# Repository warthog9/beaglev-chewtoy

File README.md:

This is a fairly simple little board targetted at the BeagleV, but likely usable for anything that uses a 2x20 pin header.

The board takes the existing 2x20 header and either via a through-hole, or smt, header extends it away from the board
(assuming the connetor is on the edge, and rotates it 180deg so if you happen to have a large heat sink, or something
else that's blocking the pins they might still be accessible for hats, etc

# Where to get one built

* OSH Park https://oshpark.com/shared_projects/uNRCdQbW

# License and Copyright
(C) John 'Warthog9' Hawley 2021
CC-BY-SA 4.0

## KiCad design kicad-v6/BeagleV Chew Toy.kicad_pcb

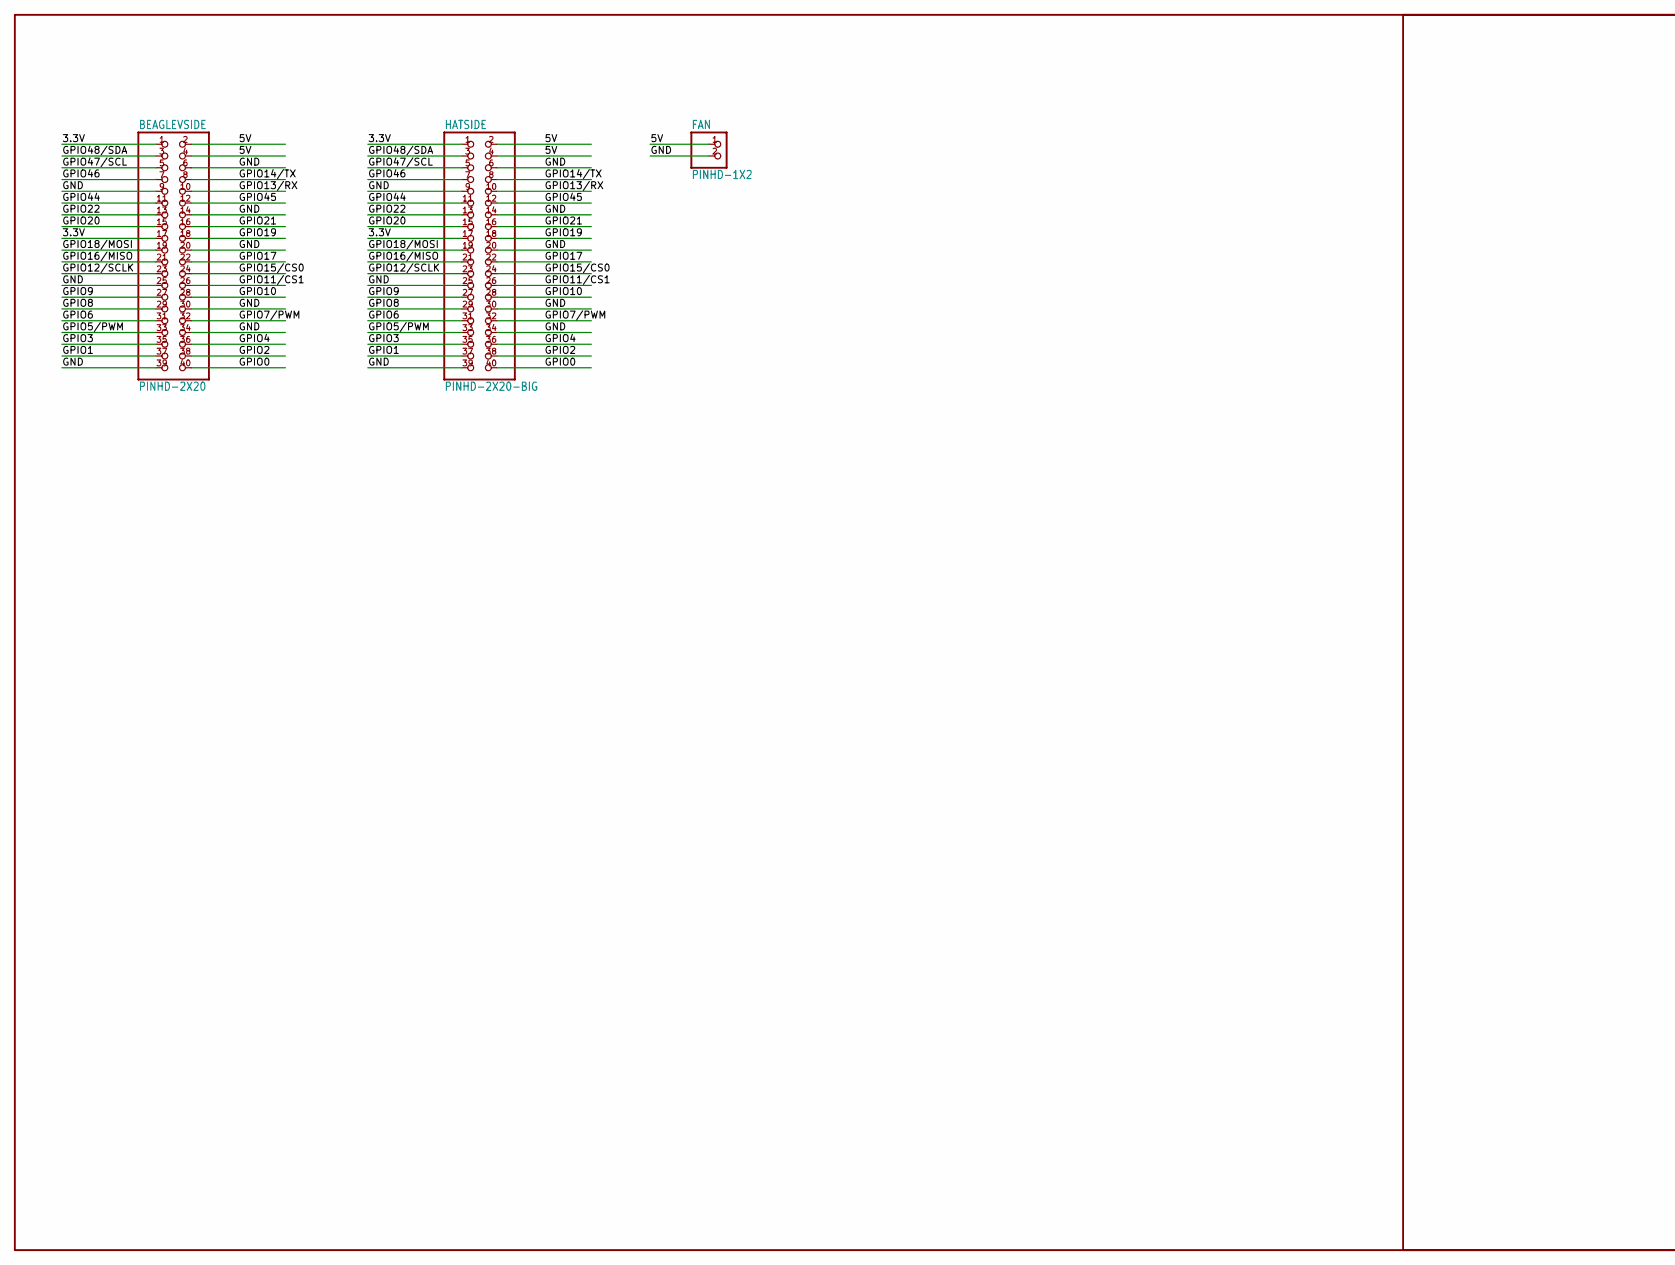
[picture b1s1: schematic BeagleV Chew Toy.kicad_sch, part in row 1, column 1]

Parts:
BEAGLEVSIDE: PINHD-2X20; 2X20
FAN: PINHD-1X2; 1X02
HATSIDE: PINHD-2X20-BIG; 2X20-BIG

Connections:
3.3V: BEAGLEVSIDE.1, BEAGLEVSIDE.17, HATSIDE.1, HATSIDE.17
5V: BEAGLEVSIDE.2, BEAGLEVSIDE.4, FAN.1, HATSIDE.2, HATSIDE.4
GND: BEAGLEVSIDE.6, BEAGLEVSIDE.9, BEAGLEVSIDE.14, BEAGLEVSIDE.20, BEAGLEVSIDE.25, BEAGLEVSIDE.30, BEAGLEVSIDE.34, BEAGLEVSIDE.39, FAN.2, HATSIDE.6, HATSIDE.9, HATSIDE.14, HATSIDE.20, HATSIDE.25, HATSIDE.30, HATSIDE.34, HATSIDE.39
GPIO0: BEAGLEVSIDE.40, HATSIDE.40
GPIO1: BEAGLEVSIDE.37, HATSIDE.37
GPIO2: BEAGLEVSIDE.38, HATSIDE.38
GPIO3: BEAGLEVSIDE.35, HATSIDE.35
GPIO4: BEAGLEVSIDE.36, HATSIDE.36
GPIO5/PWM: BEAGLEVSIDE.33, HATSIDE.33
GPIO6: BEAGLEVSIDE.31, HATSIDE.31
GPIO7/PWM: BEAGLEVSIDE.32, HATSIDE.32
GPIO8: BEAGLEVSIDE.29, HATSIDE.29
GPIO9: BEAGLEVSIDE.27, HATSIDE.27
GPIO10: BEAGLEVSIDE.28, HATSIDE.28
GPIO11/CS1: BEAGLEVSIDE.26, HATSIDE.26
GPIO12/SCLK: BEAGLEVSIDE.23, HATSIDE.23
GPIO13/RX: BEAGLEVSIDE.10, HATSIDE.10
GPIO14/TX: BEAGLEVSIDE.8, HATSIDE.8
GPIO15/CS0: BEAGLEVSIDE.24, HATSIDE.24
GPIO16/MISO: BEAGLEVSIDE.21, HATSIDE.21
GPIO17: BEAGLEVSIDE.22, HATSIDE.22
GPIO18/MOSI: BEAGLEVSIDE.19, HATSIDE.19
GPIO19: BEAGLEVSIDE.18, HATSIDE.18
GPIO20: BEAGLEVSIDE.15, HATSIDE.15
GPIO21: BEAGLEVSIDE.16, HATSIDE.16
GPIO22: BEAGLEVSIDE.13, HATSIDE.13
GPIO44: BEAGLEVSIDE.11, HATSIDE.11
GPIO45: BEAGLEVSIDE.12, HATSIDE.12
GPIO46: BEAGLEVSIDE.7, HATSIDE.7
GPIO47/SCL: BEAGLEVSIDE.5, HATSIDE.5
GPIO48/SDA: BEAGLEVSIDE.3, HATSIDE.3

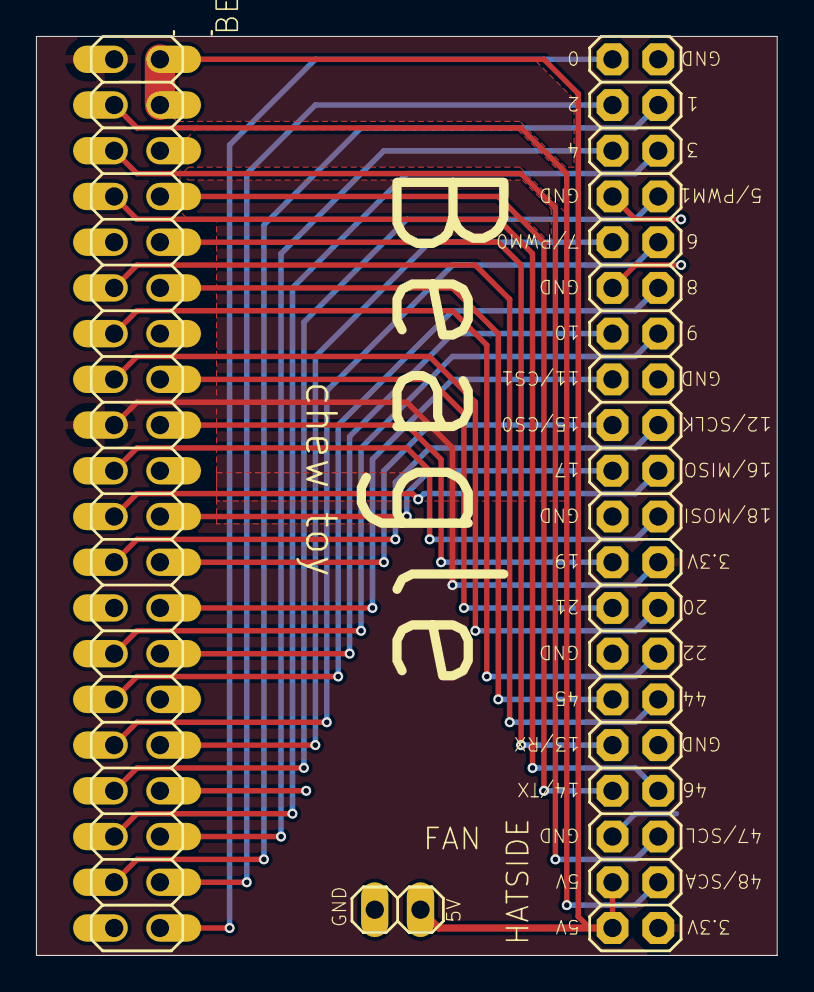
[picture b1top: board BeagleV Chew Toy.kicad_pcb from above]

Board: 2 copper layers, 41.1 x 51.1 mm, 3 parts (0 on the bottom side), 31 nets.

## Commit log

2021-04-29 Initial commit
    This adds in all the basic pieces for this board. This is one change
    past the original v1 board that was sent to production, mainly fixing a
    typo in the github url to be https vs http
2021-04-29 v1 gerbers
    This is just a result of the cam process for the v1 gerbers
2021-04-29 Update README.md
    Fixing image links
2021-05-05 Add KiCad files based on the Eagle import feature
    These files were created with latest Eagle import feature in
    KiCad v5.99 (soon to be released V6) and it is not compatible
    with older version of KiCad such as v5.1.x. Install the KiCad
    nightly dev build to view these files.

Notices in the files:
kicad-v6/BeagleV Chew Toy.kicad_pcb:
(C) 2021 John 'Warthog9' Hawley
CC-BY-SA 4.0
